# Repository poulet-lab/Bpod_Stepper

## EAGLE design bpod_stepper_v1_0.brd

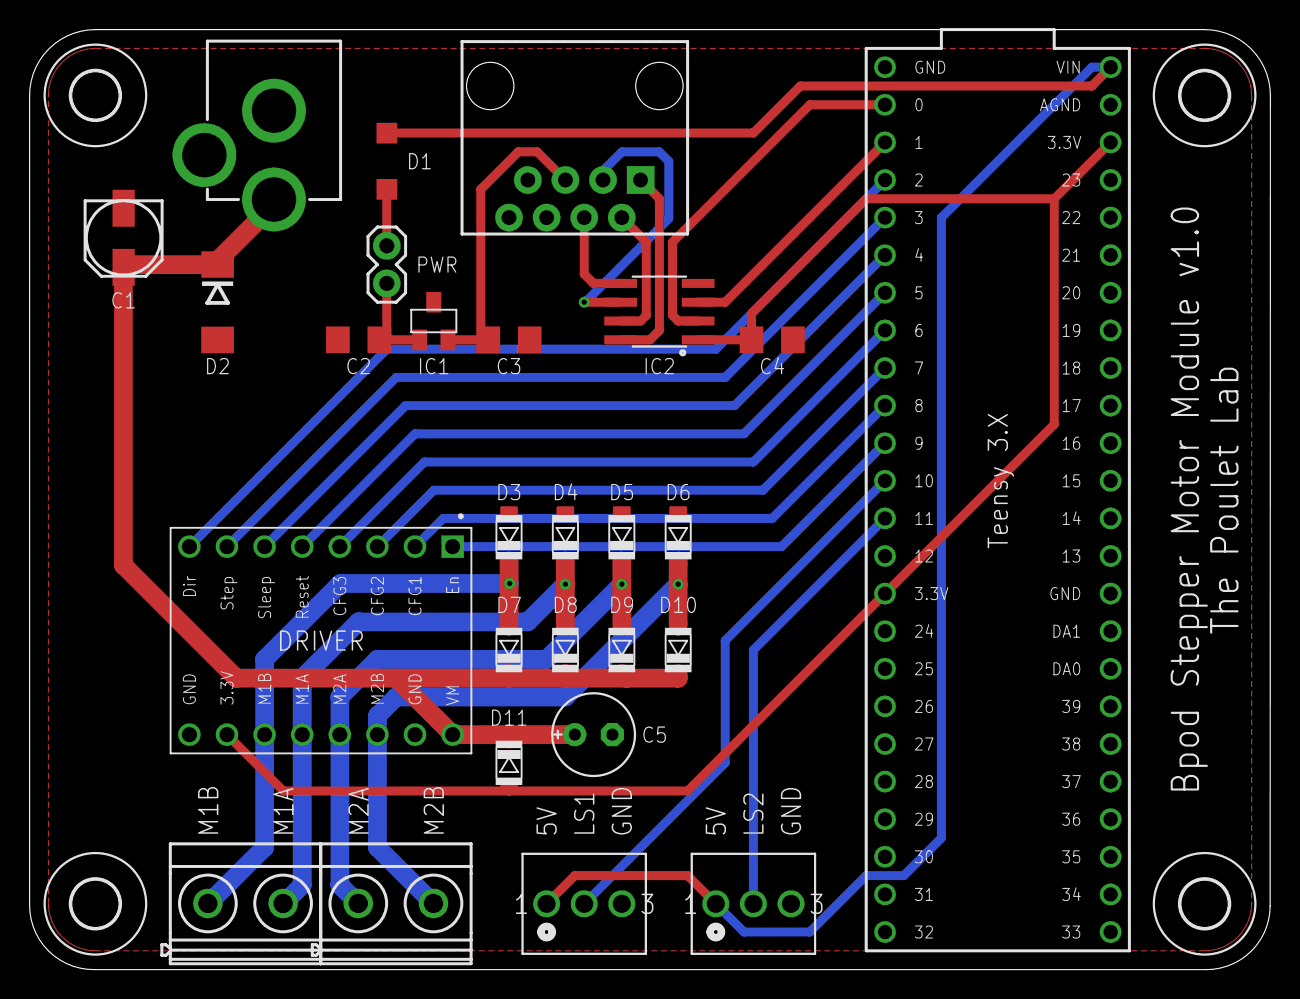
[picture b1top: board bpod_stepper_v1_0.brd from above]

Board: 2 copper layers, 83.8 x 63.5 mm, 31 parts (0 on the bottom side), 27 nets.

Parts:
1A1B, 2A2B: MKDSN1,5/2-5,08
C1: EEE-FK1H100UR
C2, C3, C4: 0.1uf; 1206@1
C5: 100µF; E2,5-6E
D1: MBR0520LT; SOD123
D2: DO214AA
D3, D4, D5, D6, D7, D8, D9, D10, D11: S310FA; SOD123
DRIVER: A4988_STEPPER_MOTOR_DRIVER_CARRIER; MODULE_A4988_STEPPER_MOTOR_DRIVER_CARRIER
IC1: LM3480-5.0; SOT-23-3
IC2: SN65HVD31DR; SO08
J8: POWER_JACK; POWER_JACK_PTH
PWR: 1X02
SENSOR1, SENSOR2: 282834-3; CONN_282834-3_TYC
U$1: TEENSY_3.6_DIL
U$2: RJ45-8PTH; RJ45-8
U$7, U$8, U$9, U$10: 3,2

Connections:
3.3V: C4.1, D11.A, DRIVER.10, IC2.1, U$1.3.3V, U$1.3.3V3
+5V: D1.C, SENSOR1.1, SENSOR2.1, U$1.VIN
CFG1: DRIVER.2, U$1.8
CFG2: DRIVER.3, U$1.7
CFG3: DRIVER.4, U$1.6
DIRECTION: DRIVER.8, U$1.2
ENABLE: DRIVER.1, U$1.9
GND: C1.CATHODE, C2.1, C3.1, C4.2, C5.-, D2.A, D3.A, D4.A, D5.A, D6.A, DRIVER.9, DRIVER.15, IC1.3, IC2.4, J8.GND, J8.GNDBREAK, SENSOR1.3, SENSOR2.3, U$1.GND, U$1.GND1, U$2.6
M1A1: 1A1B.1, D3.C, D7.A, DRIVER.11
M1B1: 1A1B.2, D4.C, D8.A, DRIVER.12
M2A1: 2A2B.1, D5.C, D9.A, DRIVER.13
M2B1: 2A2B.2, D6.C, D10.A, DRIVER.14
unnamed: IC2.8, U$2.1
unnamed: IC2.7, U$2.2
unnamed: IC2.6, U$2.3
unnamed: IC2.5, U$2.4
unnamed: C2.2, IC1.1, PWR.1
unnamed: D1.A, PWR.2
unnamed: C3.2, IC1.2, U$2.5
RESET: DRIVER.5, U$1.5
RX1: IC2.2, U$1.0
SLEEP: DRIVER.6, U$1.4
STEP: DRIVER.7, U$1.3
SWITCH1: SENSOR1.2, U$1.10
SWITCH2: SENSOR2.2, U$1.11
TX1: IC2.3, U$1.1
VMOTOR: C1.ANODE, C5.+, D2.C, D7.C, D8.C, D9.C, D10.C, D11.C, DRIVER.16, J8.PWR

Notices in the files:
parts and their libraries:
SparkFun-Capacitors: Licensing: Creative Commons ShareAlike 4.0 International - https://creativecommons.org/licenses/by-sa/4.0
SparkFun: Licensing: CC v3.0 Share-Alike You are welcome to use this library for commercial purposes.
COPYRIGHT: Copyright (C) 2016 Accelerated Designs. All rights reserved
